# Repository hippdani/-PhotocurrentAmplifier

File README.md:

# Documentation of Photocurrent Sampling Amplifier
## Daniel Hipp, TU Graz 2024
This document contains a detailed description of how to build and use a transimpedance amplifier that is specifically 
tuned to the task of photocurrent sampling (PhotCurrentSampingAmplifier = PCSA). A more concise description containing the minimum information to build and 
operate the device is contained in 
[QuickGuidePCSA_EN.pdf](https://github.com/hippdani/PhotocurrentAmplifier/blob/main/QuickGuidePCSA_EN.pdf).
More information on the design process is available in the bachelor thesis ‘Photocurrent Sampling in free Air’ by 
Daniel Hipp. Files mentioned within the document are available in the repository [PhotocurrentAmplifier](https://github.com/hippdani/PhotocurrentAmplifier).

The intended use of the PCB described in here is to amplify currents produced by a strong laser field that interacts with 
some gas or material. The PCB can be operated in a fine to high vacuum to observe ions of pure gases at low pressures.
The currents are collected at the electrodes A and B and can range from pA to µA according to the amplification gain 
that is chosen. To collect 
these currents, electrodes made out of sheet metal can be soldered onto the gold plated electrodes. To prevent the electrode
elements from acting as antenna, the whole PCB should be placed inside a metal enclosure. A more detailed description of
how to ground the enclosure is contained in chapter 5 of the [documentation](https://github.com/hippdani/PhotocurrentAmplifier/blob/main/PCS_amplifier_docu_EN.pdf)

<p align="center">
  
  <br>
  Fig. 1, Inputs and Outputs on PCB
</p>

The outputs are SMA connectors with a range from +/- 2.5 V, where linearity is guaranteed up to +/- 2 V when connected 
to a load of 1k$\Ohm$ or bigger. 

The PCB displayed above can be populated in several ways to adapt its functionality:
- Electrode A will always be an input, but B can be either:
   - an input @ 0 V bias 
   - an input with a constant bias voltage
   - a bias electrode with fixed voltage 
   - a bias electrode with externally controlled bias voltage
- The transimpedance gain and bandwidth can be set for both channels individually
- A single sided or symmetrical power supply can be used
   - populate PS1 and supply +/- 2.5 V
   - populate PS2 and supply approx. 3.3 V. The negative rail will be created by a charge pump
   
The [documentation](https://github.com/hippdani/PhotocurrentAmplifier/blob/main/PCS_amplifier_docu_EN.pdf) contains detailed information 
on how to choose a configuration and calculate the component values for different gains and bandwidths.

##Low Noise Voltage Supply
To supply a potential free voltage for the PS1 configuration it is advised to either use a battery with a linear 
regulator to maintain 5 V, or a well regulated power supply with little noise. Instructions to build a low noise regulator
suited for both batteries and switch mode power supplies is contained in the folder [LowNoisePSU](https://github.com/hippdani/PhotocurrentAmplifier/tree/main/LowNoisePSU)

##Lock In Amplifier
When used to detect photocurrents generated by a pulsed laser, the signal-to-noise ratio can be vastly improved by 
using a lock in amplifier. This lock in amplifier can be set to the reference frequency of the laser pulses and will
 then reject the noise, that is not pulsed with the reference frequency. Alternatively a Boxcar averager does a similar thing.
If no commercial lock in amplifier or boxcar avergaer is at hand, consider the on described in my other [project](https://github.com/hippdani/lockInAmplifier)
(work in progress)

##Photodiode Amplifier Modification
#TODO
- upload picture / files / BOM
- describe use
- describe the photodiodes

The circuit of the PCSA is also suited to convert the photocurrent of a photodiode with little modifications. 
The modifications are necessary to accomodate the reverse bias voltage that is needed for fast operation of a photodiode.
The high pass filter that blocks out the DC from the bias forms a band pass filter together with the intrinsic low pass 
filter of the transimpedance amplifier.

The high capacity of large are (XUV-) photodiodes limits the achievable bandwidth because stability can not be achieved 
at high frequencies and high gains (Max. gain XX Ohm for Model XY photodiode to achieve 1 MHz -3dB Bandwidth).
Additionally, the large are can act as antenna for stray signals and induce oscillations on its own.
Therefore, proper shielding is required around the photodiode.

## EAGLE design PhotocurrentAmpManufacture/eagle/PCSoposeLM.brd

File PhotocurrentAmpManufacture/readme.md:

This folder contains all the necessary information to order the photocurrent amplifier PCB from a PCB manufacturer. 
The eagle files were used successfully to order the PCB at [multi-cb](https://www.multi-circuit-boards.eu/index.html), 
using the order details shown in this [Screenshot](https://github.com/hippdani/PhotocurrentAmplifier/multicbOrderSettings). 

The gerber files should be universally accepted by any PCB manufacturer.

The BOM contains parts for different configurations of the circuit, which ones are necessary for your build can be 
determined according to the information in [PCS_Doku](https://github.com/hippdani/PhotocurrentAmplifier/PCS_Docu.pdf). Alternatively, one of the precalculated configurations from 
the [QuickGuide](https://github.com/hippdani/PhotocurrentAmplifier/QuickGuide.pdf) can be used

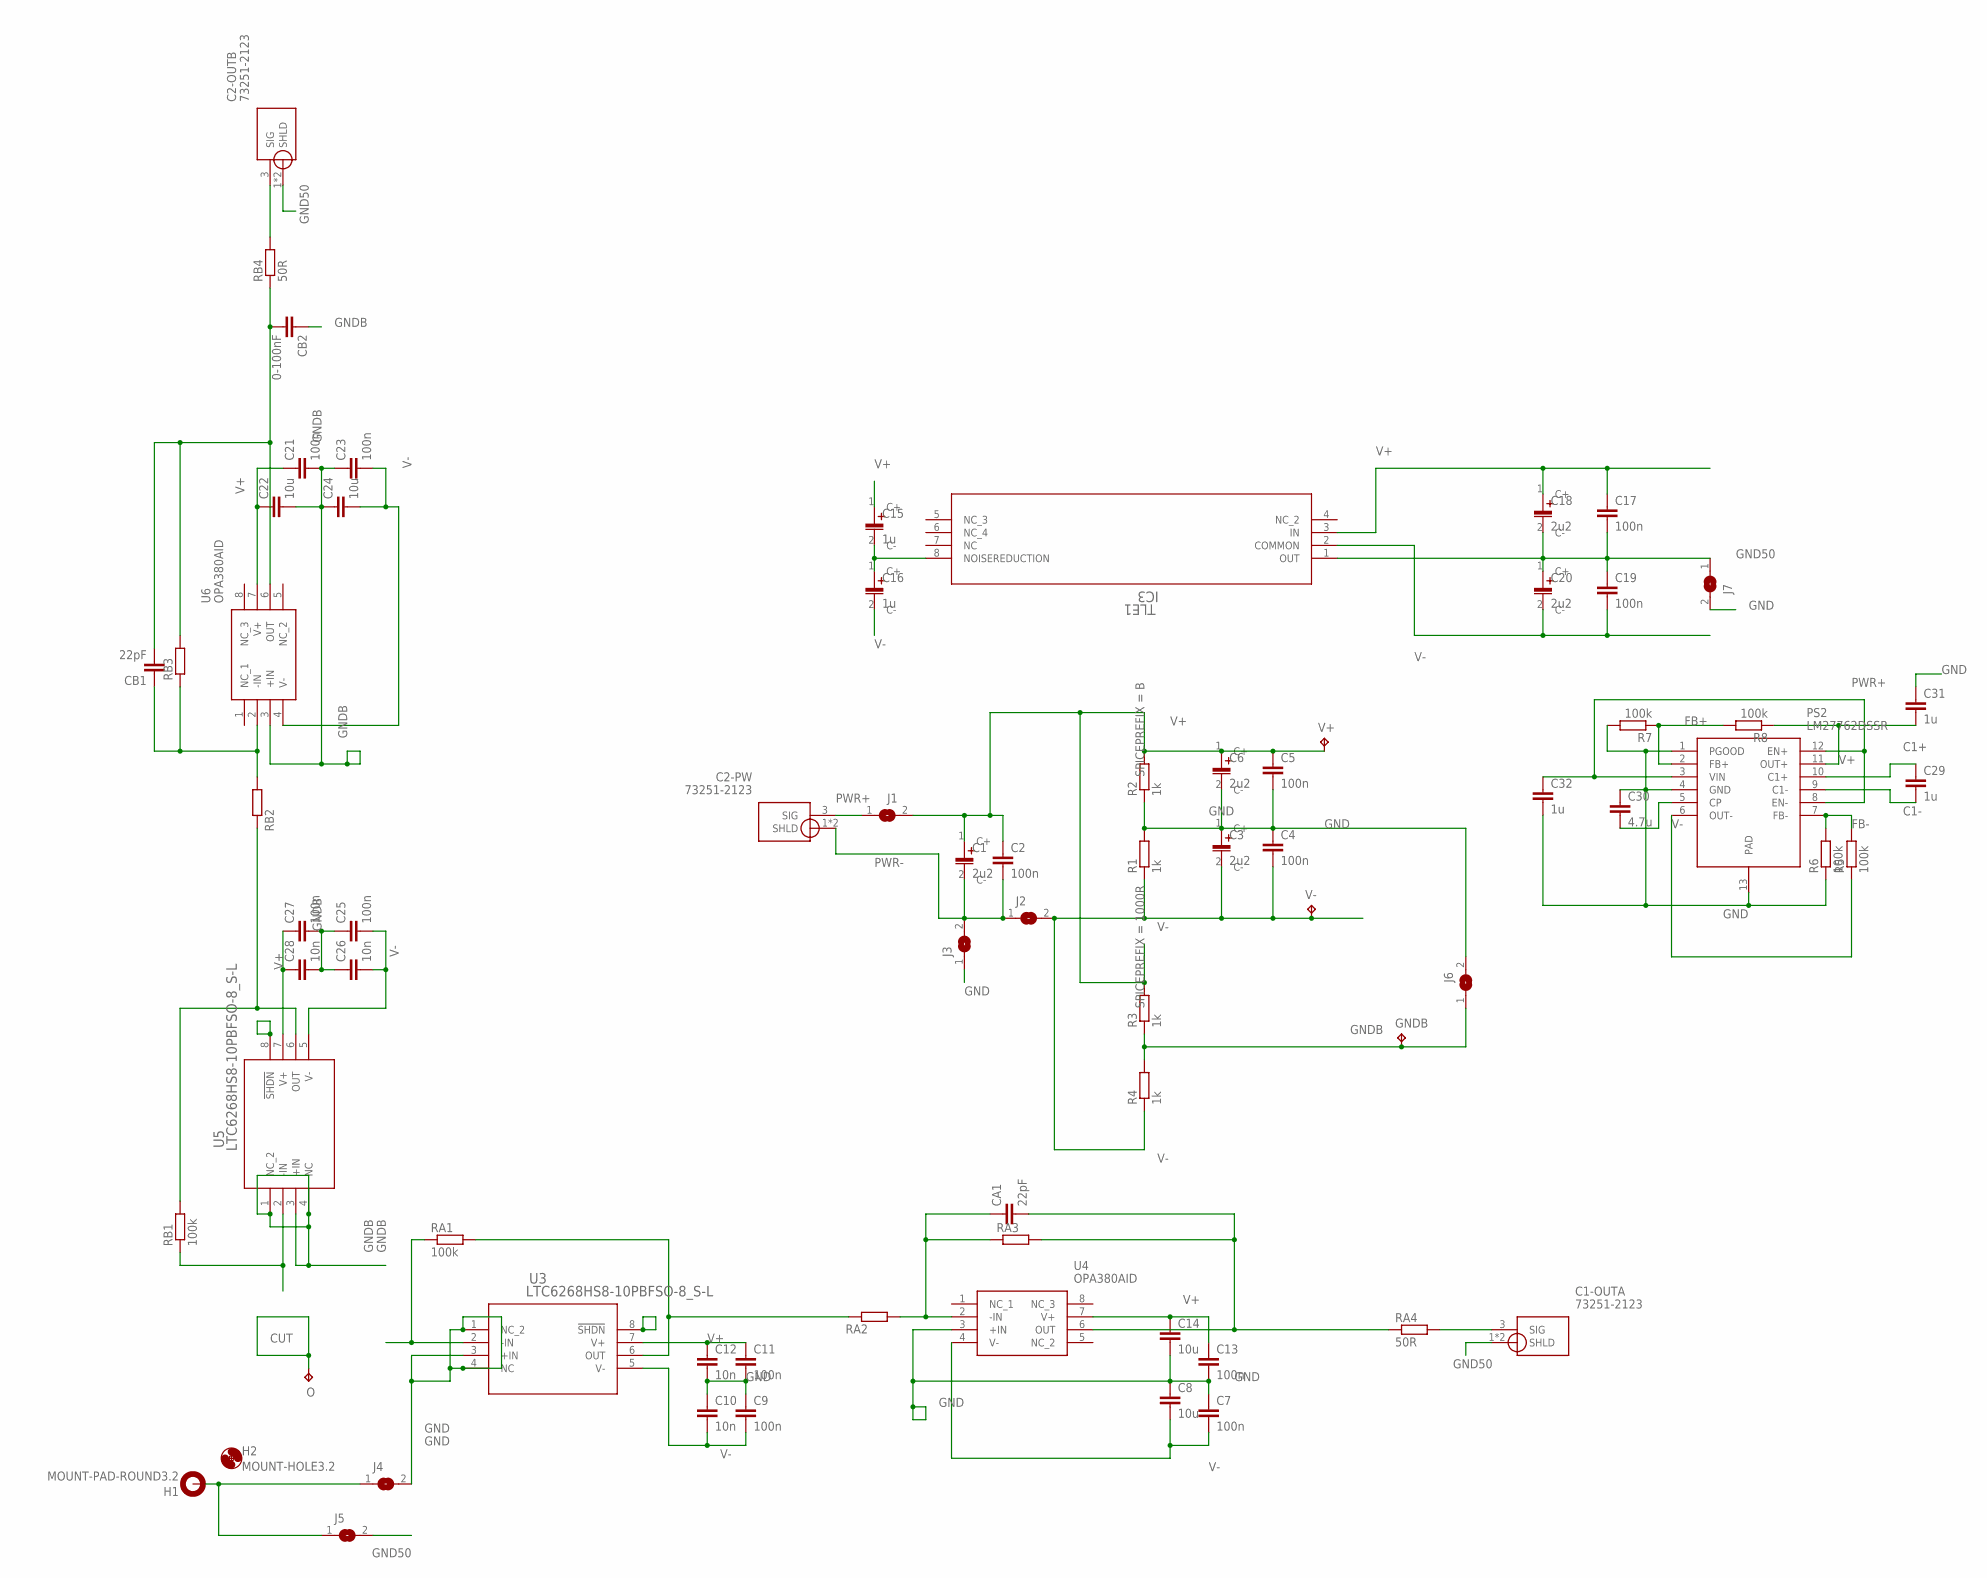
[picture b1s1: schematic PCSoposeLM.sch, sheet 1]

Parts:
C1, C3, C6, C18, C20: 2u2; C1206K
C1-OUTA, C2-OUTB, C2-PW: 73251-2123
C2, C4, C5, C7, C9, C11, C13, C17, C19, C21, C23, C25, C27: 100n; C1206K
C8, C14, C22, C24: 10u; C1206K
C10, C12, C26, C28: 10n; C1206K
C15, C16, C29, C31, C32: 1u; C1206K
C30: 4.7u; C1206K
CA1: 22pF; C1206K
CB1: 22pF; C1206K
CB2: 0-100nF; C1206K
GNDB: TPB2,54; B2,54
H1: MOUNT-PAD-ROUND3.2; 3,2-PAD
H2: MOUNT-HOLE3.2; 3,2
J1, J2, J3, J4, J5, J6, J7: SJ
O: TPTP06R; TP06R
PS2: LM27762DSSR; SON50P200X300X80-13N
R1, R2, R3, R4: 1k; R1206
R5, R6, R7, R8: 100k; R0805
RA1: 100k; R1206
RA2, RA3: R-EU_R1206; R1206
RA4: 50R; R1206
RB1: 100k; R1206
RB2, RB3: R-EU_R1206; R1206
RB4: 50R; R1206
TLE1: IC3; D8-M
U3, U5: LTC6268HS8-10PBFSO-8_S-L; SO-8_S-L
U4, U6: OPA380AID; SOIC127P600X175-8N
V+: TPB2,54; B2,54
V-: TPB2,54; B2,54

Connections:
C1+: C29.1, PS2.10 (C1+)
C1-: C29.2, PS2.9 (C1-)
CUT: O.TP
EXTGND: H1.B3,2, J4.1, J5.1
FB+: PS2.2 (FB+), R7.1, R8.2
FB-: PS2.7 (FB-), R5.2, R6.2
GND: C3.1 (C+), C4.1, C5.2, C6.2 (C-), C7.1, C8.1, C9.1, C10.1, C11.2, C12.2, C13.2, C14.2, C30.1, C31.1, C32.2, J3.1, J4.2, J6.2, J7.2, PS2.1 (PGOOD), PS2.4 (GND), PS2.13 (PAD), R1.2, R2.1, R6.1, R7.2, U3.1 (NC_2), U3.3 (+IN), U3.4 (NC), U4.3 (+IN)
GND50: C1-OUTA.1 (SHLD), C1-OUTA.2 (SHLD), C2-OUTB.1 (SHLD), C2-OUTB.2 (SHLD), C17.2, C18.2 (C-), C19.1, C20.1 (C+), J5.2, J7.1, TLE1.1 (OUT)
GNDB: C21.2, C22.2, C23.1, C24.1, C25.1, C26.1, C27.2, C28.2, CB2.1, GNDB.TP, J6.1, R3.1, R4.2, U5.1 (NC_2), U5.3 (+IN), U5.4 (NC), U6.3 (+IN)
INA: RA1.1, U3.2 (-IN)
INB: RB1.1, U5.2 (-IN)
unnamed: C15.2 (C-), C16.1 (C+), TLE1.8 (NOISEREDUCTION)
unnamed: RA1.2, RA2.2, U3.6 (OUT)
unnamed: C30.2, PS2.5 (CP)
unnamed: CA1.1, RA2.1, RA3.1, U4.2 (-IN)
unnamed: CA1.2, RA3.2, RA4.1, U4.6 (OUT)
unnamed: C1-OUTA.3 (SIG), RA4.2
unnamed: RB1.2, RB2.2, U5.6 (OUT)
unnamed: CB1.1, RB2.1, RB3.1, U6.2 (-IN)
unnamed: CB1.2, CB2.2, RB3.2, RB4.1, U6.6 (OUT)
unnamed: C2-OUTB.3 (SIG), RB4.2
PWR+: C2-PW.3 (SIG), C32.1, J1.1, PS2.3 (VIN), PS2.8 (EN-), PS2.12 (EN+)
PWR-: C1.2 (C-), C2.2, C2-PW.1 (SHLD), C2-PW.2 (SHLD), J2.1, J3.2
V+: C1.1 (C+), C2.1, C5.1, C6.1 (C+), C11.1, C12.1, C13.1, C14.1, C15.1 (C+), C17.1, C18.1 (C+), C21.1, C22.1, C27.1, C28.1, C31.2, J1.2, PS2.11 (OUT+), R2.2, R3.2, R8.1, TLE1.3 (IN), U3.7 (V+), U4.7 (V+), U5.7 (V+), U6.7 (V+), V+.TP
V-: C3.2 (C-), C4.2, C7.2, C8.2, C9.2, C10.2, C16.2 (C-), C19.2, C20.2 (C-), C23.2, C24.2, C25.2, C26.2, J2.2, PS2.6 (OUT-), R1.1, R4.1, R5.1, TLE1.2 (COMMON), U3.5 (V-), U4.4 (V-), U5.5 (V-), U6.4 (V-), V-.TP

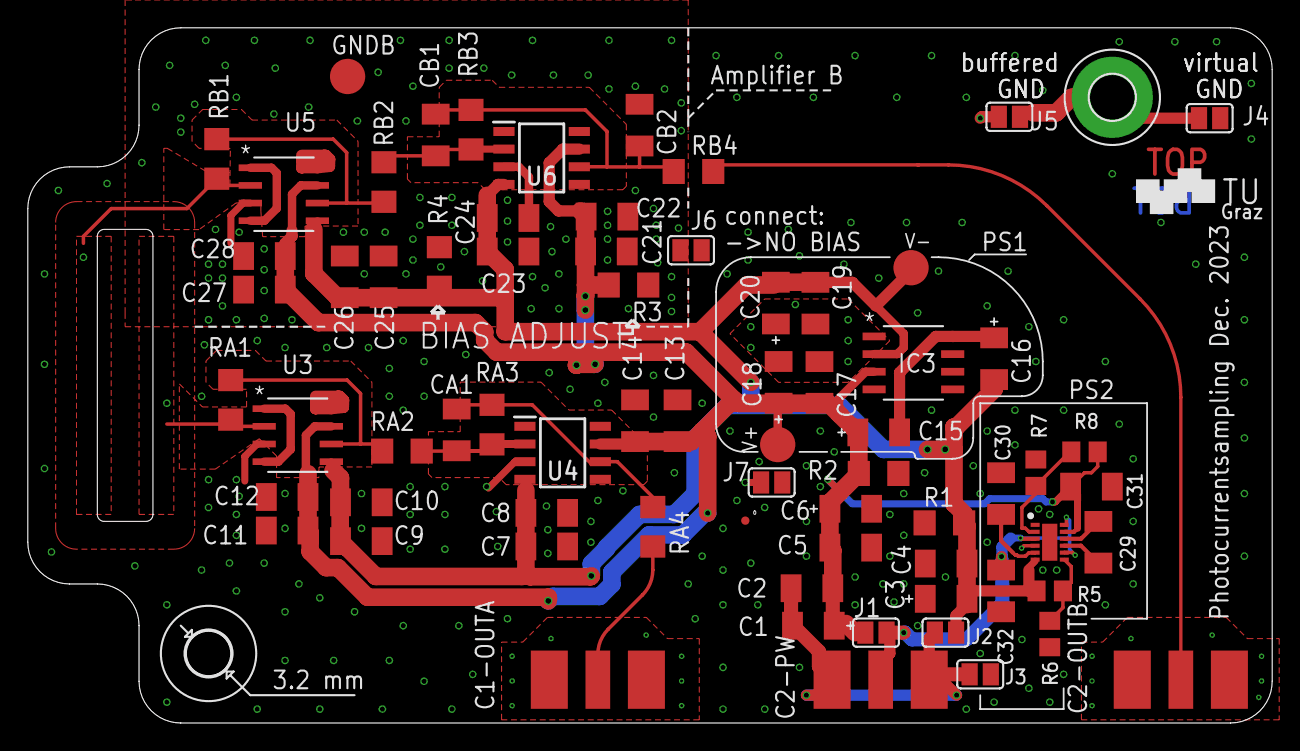
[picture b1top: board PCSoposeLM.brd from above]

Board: 4 copper layers, 89.5 x 50.0 mm, 73 parts (0 on the bottom side), 24 nets.

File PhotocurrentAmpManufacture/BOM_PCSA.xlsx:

() = variable |  | [] = optional / alternative |  | Powersupply options PS1 / PS2 | Jumper open = n, Jumper connected = y
Qty | Value | Device | Package | Parts | Description | Hersteller Nr.
2 | (10M) (100k - 100M) | R-EU_R1206 | R1206 | RA1, RB1 | Precision, thinfilm or metalfilm | ERA8AEB105V / MCA1206MD1005BP100
2 | (10k) (1k-100k) | R-EU_R1206 | R1206 | RA2, RB2 | 2nd Stage amplification feedback resistor
2 | (10k) (1k-100k) | R-EU_R1206 | R1206 | RA3, RB3 | 2nd Stage amplification feedback resistor
1 | [0-100nF] | C-EUC1206K | C1206K | CB2 | Bias Low Pass filter if no Amp2 installed
2 | (22pF) | C-EUC1206K | C1206K | CA1, CB1 | NP0 feedback kerko
2 | 50R | R-EU_R1206 | R1206 | RA4, RB4 | 47R-53R impedance matching resistor
13 | 100n | C-EUC1206K | C1206K | C2, C4, C5, C7, C9, C11, C13, C17, C19, C21, C23, C25, C27 | 10% 50V X7R | C1206C104K5RACAUTO
4 | 10n | C-EUC1206K | C1206K | C10, C12, C26, C28 | 10% 50V X7R | C1206C103K5RACTU
9 | 10uF | C-EU_POL / C-EUC1206K | C1206K | C8, C14, C22, C24, C1, C3, C6, C18, C20 | Tantal elko 1206 | TPSA106K010R0900
4 | 1k | R-EU_R1206 | R1206 | R1, R2, R3, R4 | Precision 1k 0.1% (Metalfilm, Thinfilm) | ERA8AEB102V
2 | LTC6268HS8-10PBFSO-8_S-L | LTC6268HS8-10PBFSO-8_S-L | SO-8_S-L | U3, U5
2 | OPA380AID | OPA380AID | SOIC127P600X175-8N | U4, U6 | Texas Instruments OPA380AI | OPA380AID
3 | SMA Jack | 73251-2123 | 73251-2123 | C1-OUTA, C2-OUTB, C2-PW | SMA Jack PCB Edge Mount 50 | 526-5785
4 | [100k @ PS2] | R-EU_R0805 | R0805 | R5, R6, R7, R8
3 | [1u @ PS2] | C-EUC1206K | C1206K | C29, C31, C32 | kerko switching
1 | [4.7u @ PS2] | C-EUC1206K | C1206K | C30
1 | [LM27762DSSR @ PS2] | LM27762DSSR | SON50P200X300X80-13N | PS2 | LDO Voltage Regulators and neg. switching | LM27762DSSR
2 | [1u @ PS1] | C-EU_POL | C1206K | C15, C16 | Tantal elko 1206 | TPSA105K035R3000
1 | [TLE2426 @ PS1] | TLE2426CDD8-M | D8-M | IC3
7 | () | Jumper |  | J1, J2, J3, J4, J5, J6, J7 | Select appropriate Jumpers
6 | () | Jumper PS1 |  | J1=y, J2=y, J3=n, J4 OR J5, J7=IF J4 AND J5 | Select appropriate Jumpers
6 | () | Jumper PS2 |  | J1=n, J2=n, J3=y, J4=y, J5=y, J7=y | Select appropriate Jumpers
1 | () | Jumper Amp A & B |  | J6=y | Select appropriate Jumpers
1 | () | Jumper Amp A & ext. Bias |  | J6=y | Select appropriate Jumpers
1 | () | Jumper Amp A & int. Bias |  | J6=n | Select appropriate Jumpers

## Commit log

2024-11-28 Create README.md
    First commit and test of how GitHub handels images in md
2024-11-28 Add Low Noise PSU related Files via upload
2024-11-28 Create readme.md for LowNoisePSU folder
2024-11-28 Moved Low Noise Powersupply Doku.pdf to LowNoisePSU/Low Noise Powersupply Doku.pdf
2024-11-28 Move LowNoisePSU_BOM.csv to LowNoisePSU/LowNoisePSU_BOM.csv
2024-11-28 Move LowNoisePSU_2023-09-27.zip to LowNoisePSU/LowNoisePSU_2023-09-27.zip
2024-11-28 Added PCS PCB files via upload
2024-11-29 Update README.md
    Math mode test
2024-11-29 Update LICENSE.md for TU Graz Logo
2024-12-10 Added Quick Guide, LN:PSU_docu in english, BOM and started TODO. Added some links to the readmes
2024-12-10 Added 3D print files
2024-12-10 Added .docx sources, updated some of those, added Photodiode Mod, updated root README.md

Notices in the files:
parts and their libraries:
COPYRIGHT: Copyright (C) 2023 Ultra Librarian. All rights reserved.
